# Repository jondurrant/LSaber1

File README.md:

# LSaber1
IOT Saber Wall Light based on Raspberry PI Pico, ESP-01S and WS2812 LEDs.

PIR and Switch activated wall light. Works as a group able to turn each other on and off via MQTT hub topics. 

# Hardware
+ Raspberry Pico
+ ESP-01S (1Mb) running ESP-AT 2.1
+ WS2812 144 LED strip
+ AM312 PIC
+ RGB CC LED
+ Resistors and Caps as in Schema
+ 5Amp 5Volt power supply
+ 5 Amp Fuse and 100C Thermal Fuse
+ M2 inserts for scew fixing of PCB to case and pommel onto case

## Schema 
A circuit diagram is available in KICAD format. Included in PCB folder.

Warning: The LEDs will draw 4Amps of current. You should assure yourself that the circuit and wiring can safely deliver that current. 

## ESP-01S
I got very cheap pack of ESP-01S but they came with 1Mb flash. Latest version of ESP-AT, version 2.2, requires 2MB. 

Fortunatly Jandrassy has built a working 2.1 firmware for 1MB. This is on github at: https://github.com/jandrassy/WiFiEspAT

To reliably upload the firmware to ESP-01S requires the RST IO0 to get pulled to zero and the released. Some further inform on how to do this at: https://blog.tiga.tech/flashing-esphome-firmware-to-esp-01s/

I used the RPI 4 to upload the firmware and the esptool.py. I had to drop frequency to 40m and change upload mode to dout in the download.config file. Then use the command
esptool.py --port /dev/ttyS0 write_flash @download.config

## Case
Case is 3D printed in PLA. I've modelled the case and wall mounts for the case in OpenSCAD. The model and SLA files available in the 3dmodels folder.

## Blade
Blade is a 20mm x 3mm x 1000mm OPAL Acrylic Tube. You can find these on ebay, though I found ebay quite expensive. Bought mine from [The Clear Plastic Shop](https://clearplastictube.co.uk/opal-acrylic-tube) in the UK. 

# Software

## C++ - For Raspberry PICO
+ [lwesp](https://github.com/MaJerle/lwesp): library for talking to ESP-AT over serial
+ + [forkedlwesp](https://github.com/jondurrant/lwespFork) Forked to allow MQTT over SSL. 
+ [FreeRTOS-Kernel](https://github.com/FreeRTOS/FreeRTOS-Kernel): dependency for lwesp
+ [json-maker](https://github.com/rafagafe/json-maker)
+ [tiny-json](https://github.com/rafagafe/tiny-json)
+ [RtosComponents](https://github.com/jondurrant/RtosComponents) - my library for watchdog and RGB PWM control
+ [twinThingPicoESP](https://github.com/jondurrant/twinThingPicoESP) - IOT Library
+ [PicoLED](https://github.com/ForsakenNGS/PicoLED) - Manage the WS2812 LEDs

## Python -  Management Software
+ [TwinThingPyMQTT](https://github.com/jondurrant/TwinThingPyMQTT) - Python version of IOT Library, including TwinMgr which is how the management software talks to all the devices.
+ Python3
+ dotmap
+ numpy
+ paho-mqtt
+ pandas
+ PyMySQL
+ pyOpenSSL
+ SQLAlchemy
+ [twinThing](https://github.com/jondurrant/twinThing) 
+ mysql Db
+ [emqx](https://www.emqx.io/) using Mysql authentication 
+ [Joern Weissenborn LCARS](http://joernweissenborn.github.io/lcars/) - LCARS Look and feel

## Python Test Code
Some test code to interact with the api are included in py/test folder. They expect some environment variables to point to the MQTT hub and credentials.
+ MQTT_USER - Username and Client Id to connect to MQTT
+ MQTT_PASSWD - Password to authenticate against MQTT
+ MQTT_HOST - Hostname of MQTT server
+ MQTT_PORT - Port that MQTT is listen on, normally 1883

# Build and Deploy

##Clone project
'''
git clone --recurse-submodules https://github.com/jondurrant/LSaber1
'''
main.cpp include "Credentials.env" for the Wifi AP name and passwd, MQTT Host, Port, Username and password. I've not included this file in the repo. Please create one looking something like this:

``` C++
#define SID "SID"
#define PASSWD "PWD"

#define MQTTHOST "IP"
#define MQTTPORT 1883
#define MQTTUSER "jon"
#define MQTTPASSWD "PWD"
```

## To build C++:
``` bash
mkdir build
cd build
cmake ..
make
make install (only work if you used my config setup in the Pico Intro course as does SWD upload of code direct from make).
```

For more on how I use a Raspberry PI to build, deploy code  and debug the Pico see my course on [Udemy](https://www.udemy.com/course/introduction-to-c-development-environment-for-raspberry-pico/?referralCode=875319E04F95C9EC3414)

## Python Management Deployment
I have included a Docker file to build an image for the management software. It manipulates the Python path to include the right libraries, along with loading some from requirements.txt.

## EMQX
Setup EMQX using mysql authentication and acl. The [TwinThingPyMQTT](https://github.com/jondurrant/TwinThingPyMQTT) repo include the DDL to create the required tables.

Lights authenticate using the MAC address of the device for Client Id, Username and Password. They will require permissions within EMQX to access:
```
[
	{
	  "topic": "GRP/ALL/TPC/#",
	  "action": "sub",
	  "access": "allow"
	},
	{
	  "topic": "TNG/$CLIENTID/#",
	  "action": "pubsub",
	  "access": "allow"
	},
	{
	  "topic": "GRP/saber/TPC/#",
	  "action": "pubsub",
	  "access": "allow"
	}
]
```
The Management software will need access to:
```
[
	{
	  "topic": "GRP/ALL/TPC/#",
	  "action": "sub",
	  "access": "allow"
	},
	{
	  "topic": "TNG/$CLIENTID/#",
	  "action": "pubsub",
	  "access": "allow"
	},
	{
	  "topic": "GRP/saber/TPC/#",
	  "action": "pubsub",
	  "access": "allow"
	},
	{
	  "topic": "GRP/saber/TWIN/RES",
	  "action": "sub",
	  "access": "allow"
	},
	{
	  "topic": "GRP/saber/TWIN/GET",
	  "action": "pub",
	  "access": "allow"
	},
	{
	  "topic": "GRP/saber/TWIN/SET",
	  "action": "pub",
	  "access": "allow"
	}
]
```

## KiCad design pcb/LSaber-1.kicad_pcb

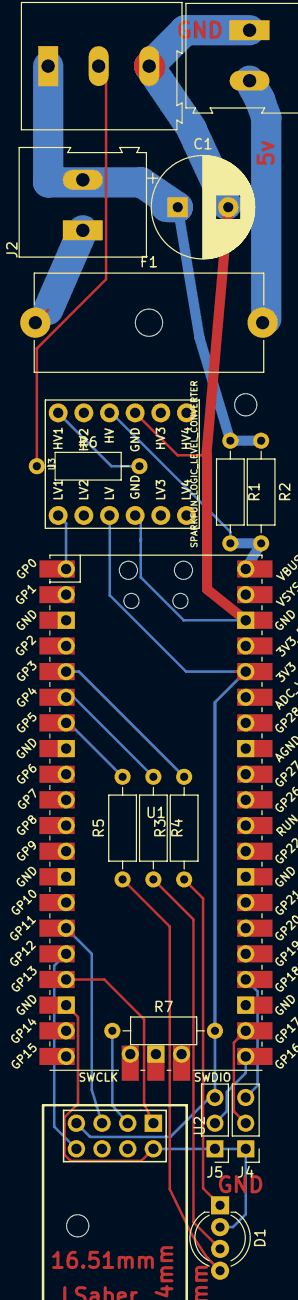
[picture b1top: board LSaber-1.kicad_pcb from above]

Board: 2 copper layers, 18 parts (0 on the bottom side), 22 nets.

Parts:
C1: CP; CP_Radial_D10.0mm_P5.00mm
D1: LED_RCGB; LED_D5.0mm-4_RGB_Wide_Pins
F1: Fuse 5A; Fuseholder_Cylinder-5x20mm_Schurter_0031_8201_Horizontal_Op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
J1, J2: Screw_Terminal_01x02; TerminalBlock_Altech_AK300-2_P5.00mm
J3: Screw_Terminal_01x03; TerminalBlock_Altech_AK300-3_P5.00mm
J4, J5: Conn_01x03_Male; PinHeader_1x03_P2.54mm_Vertical
R1, R2: 10R; R_Axial_DIN0207_L6.3mm_D2.5mm_P10.16mm_Horizontal
R3, R4, R5: 92R; R_Axial_DIN0207_L6.3mm_D2.5mm_P10.16mm_Horizontal
R6: 330R; R_Axial_DIN0207_L6.3mm_D2.5mm_P10.16mm_Horizontal
R7: 10K; R_Axial_DIN0207_L6.3mm_D2.5mm_P10.16mm_Horizontal
U1: Pico; RPi_Pico_SMD_TH
U2: ESP-01v090; ESP-01
U3: SPARKFUN_LOGIC_LEVEL_CONVERTER

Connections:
+3V3: J5.3, R7.2, U1.36, U2.7, U3.LV
+5V: F1.2, J1.2
GND: C1.2, D1.2, J1.1, J3.3, J4.1, J5.1, U1.18, U1.38, U2.2, U3.GND1, U3.GND2
unnamed: C1.1, J2.2, J3.1, R1.1, R2.1
unnamed: D1.1, R3.1
unnamed: D1.3, R4.2
unnamed: D1.4, R5.1
unnamed: J3.2, R6.1
unnamed: F1.1, J2.1
unnamed: J4.2, U1.22
unnamed: J4.3, U1.24
unnamed: J5.2, U1.21
unnamed: R1.2, R2.2, U1.40, U3.HV
unnamed: R3.2, U1.5
unnamed: R4.1, U1.6
unnamed: R5.2, U1.7
unnamed: R6.2, U3.HV1
unnamed: R7.1, U2.3
unnamed: U1.1, U3.LV1
unnamed: U1.15, U2.5
unnamed: U1.16, U2.8
unnamed: U1.17, U2.1

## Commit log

2021-11-28 Initial version
2021-11-29 Second core added running ws2812b, primitive example
2021-12-03 Second core has manager class and timeout. Sending messages back on time otu of blade lights
2021-12-04 PIR and Switch working
2021-12-08 Blade Colour and Sequence added
2021-12-08 New Hope blade animation added
2021-12-08 Restructured to allow base class with most of animation code
2021-12-20 Moved to use MAC as ID and username. Added in Group control
2021-12-21 Group Communication to sync light status.
2021-12-21 PIR activity keeps light on
2021-12-22 Added in additiona state members
2021-12-22 Blade checking time.
2021-12-23 Added Seqs
2021-12-24 Added Alert seq
2021-12-24 Alarm Seq Added
2021-12-24 Added Alert and group notification of alert.
2022-01-03 Added brightness control to BladeColour and use on some sequences
2022-01-04 Trying to control false possitive PIR
2022-01-11 Buffer space issue
2022-01-13 Fixed bug with change notification not working due to library having some 8bit references
2022-01-21 Needs comments and debug removed. Issue with nrgb not being set
2022-01-22 Fix bug with nrgb and added clock
2022-01-24 Added comments and switched to support TLS
2022-01-24 Tested night mode ignore peer turn on messages, but respond to remote and local state requests
2022-01-28 Fixed issues with expanding to 144led blade
2022-02-21 Docker Deploy version
2022-02-21 Bump numpy from 1.20.1 to 1.21.0 in /py
    Bumps [numpy](https://github.com/numpy/numpy) from 1.20.1 to 1.21.0.
    - [Release notes](https://github.com/numpy/numpy/releases)
    - [Changelog](https://github.com/numpy/numpy/blob/main/doc/HOWTO_RELEASE.rst.txt)
    - [Commits](https://github.com/numpy/numpy/compare/v1.20.1...v1.21.0)
    ---
    updated-dependencies:
2022-02-27 Bug fix in Python manager
2022-03-01 Wifi Reconnect bug
2022-03-10 Working code with DEBUG turned on.
2022-03-10 Fix security vunrability.
2022-03-21 Bump waitress from 2.0.0 to 2.1.1 in /py
    Bumps [waitress](https://github.com/Pylons/waitress) from 2.0.0 to 2.1.1.
    - [Release notes](https://github.com/Pylons/waitress/releases)
    - [Changelog](https://github.com/Pylons/waitress/blob/master/CHANGES.txt)
    - [Commits](https://github.com/Pylons/waitress/compare/v2.0.0...v2.1.1)
    ---
    updated-dependencies:
2022-06-22 Bump numpy from 1.21.0 to 1.22.0 in /py
    Bumps [numpy](https://github.com/numpy/numpy) from 1.21.0 to 1.22.0.
    - [Release notes](https://github.com/numpy/numpy/releases)
    - [Changelog](https://github.com/numpy/numpy/blob/main/doc/HOWTO_RELEASE.rst)
    - [Commits](https://github.com/numpy/numpy/compare/v1.21.0...v1.22.0)
    ---
    updated-dependencies:
2023-05-01 Bump flask from 2.0.3 to 2.3.2 in /py
    Bumps [flask](https://github.com/pallets/flask) from 2.0.3 to 2.3.2.
    - [Release notes](https://github.com/pallets/flask/releases)
    - [Changelog](https://github.com/pallets/flask/blob/main/CHANGES.rst)
    - [Commits](https://github.com/pallets/flask/compare/2.0.3...2.3.2)
    ---
    updated-dependencies:
